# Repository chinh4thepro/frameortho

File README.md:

# frameortho
testing out if a custom keyboard for a framework 13 would work. based off of sweep, slightly modified.

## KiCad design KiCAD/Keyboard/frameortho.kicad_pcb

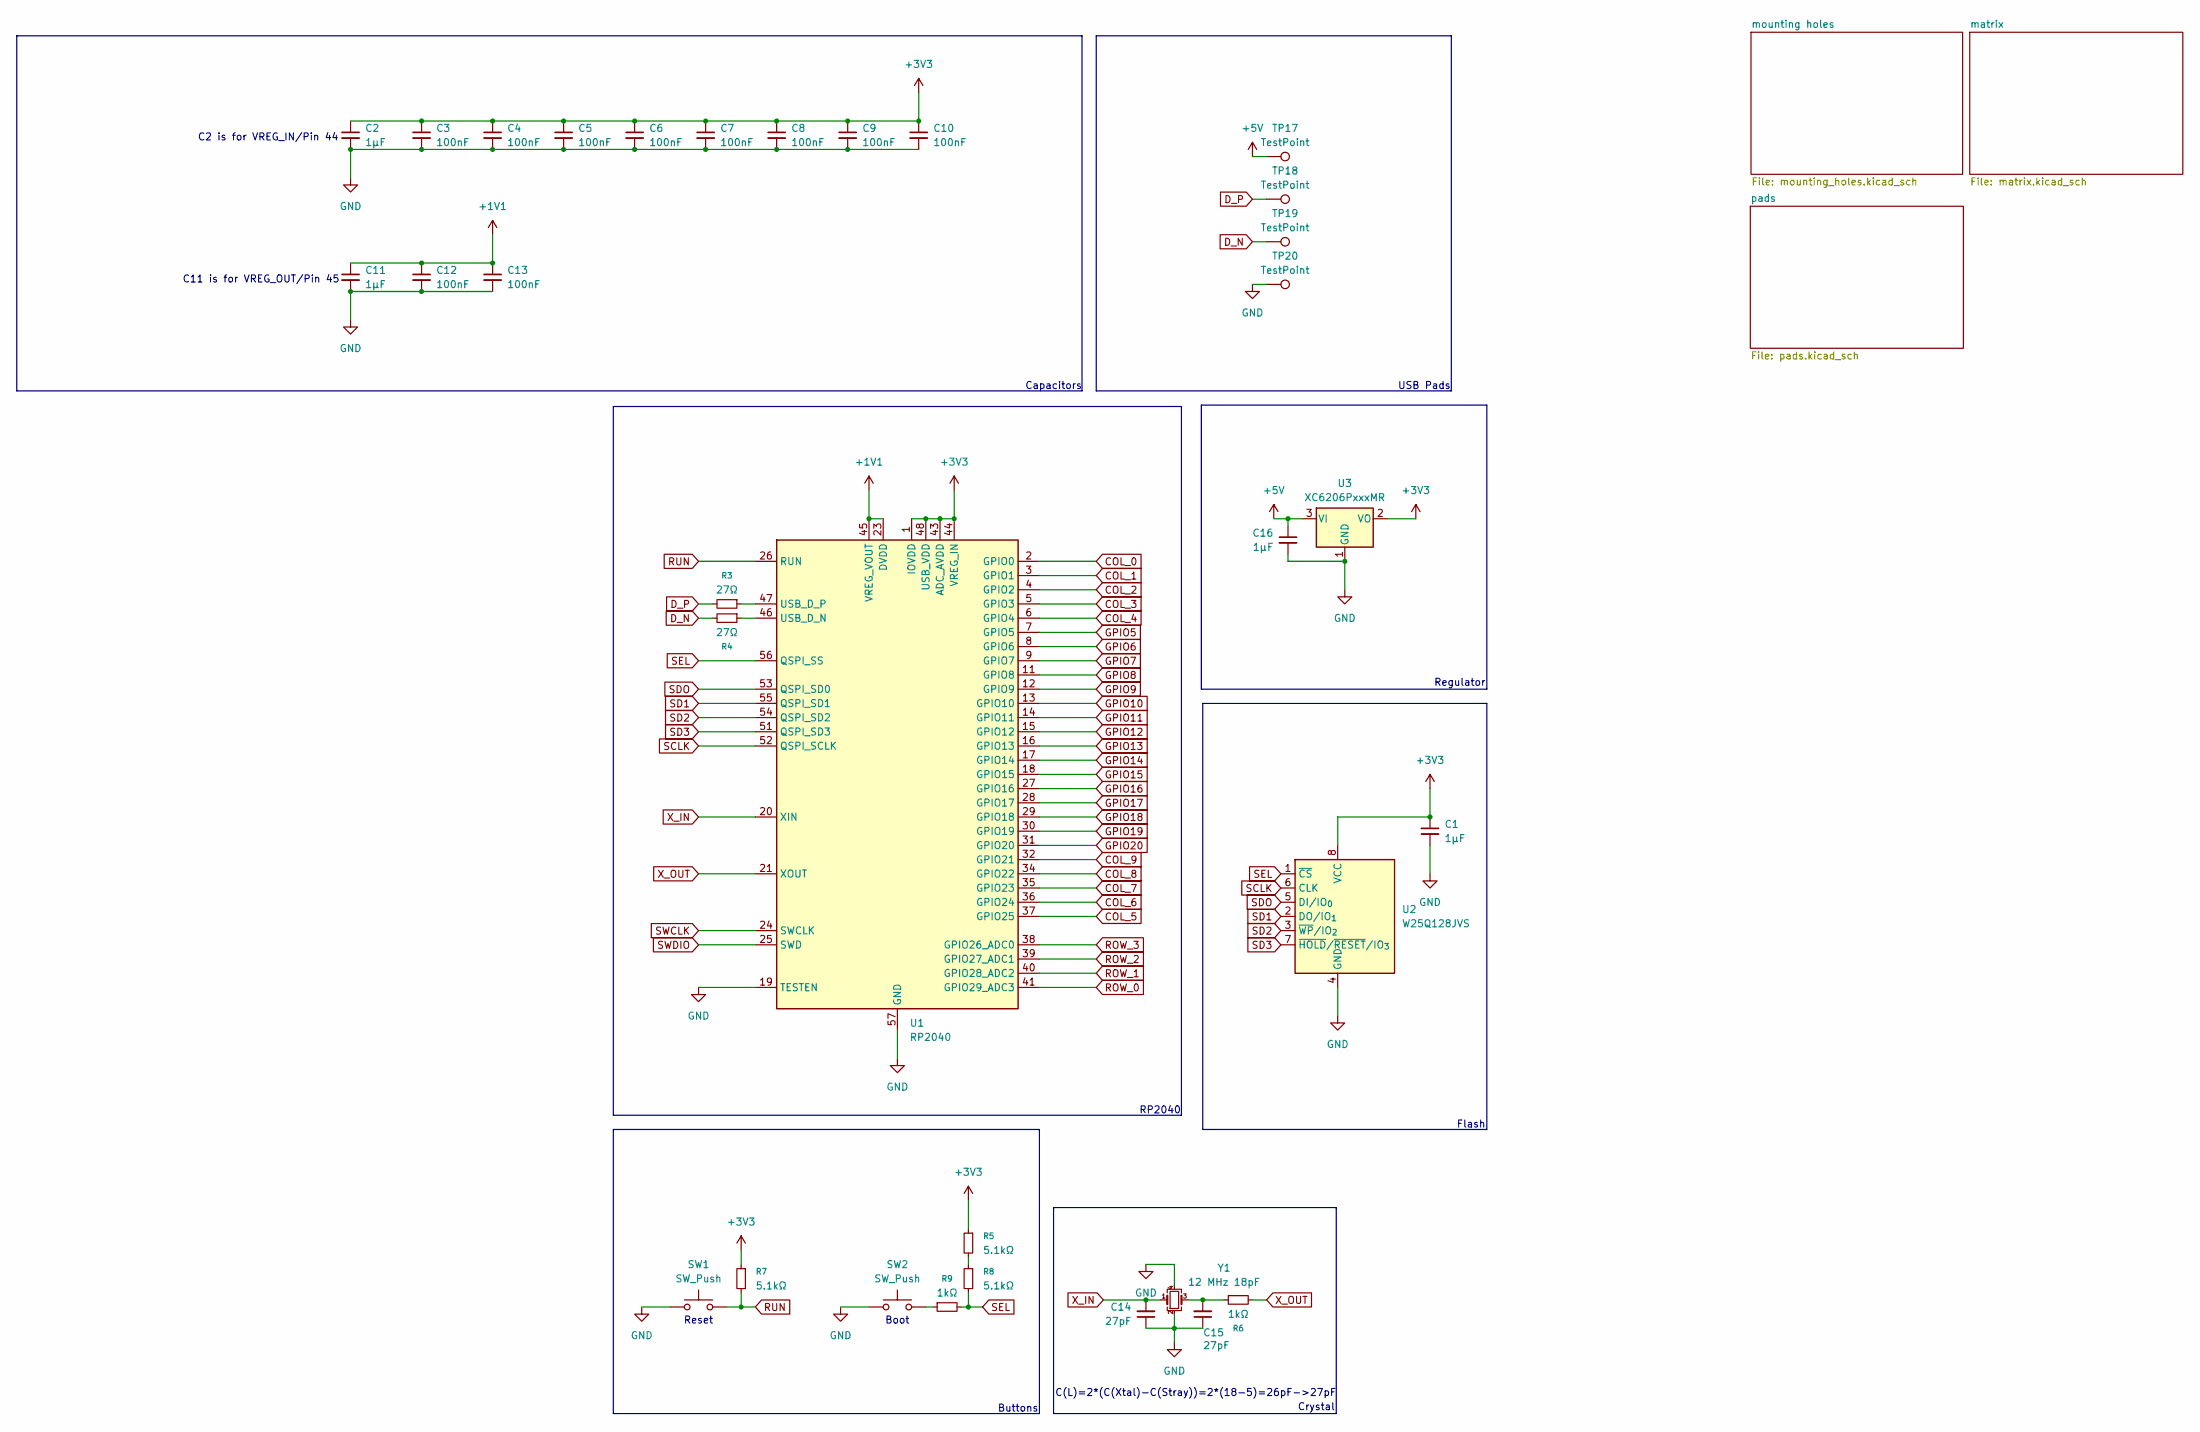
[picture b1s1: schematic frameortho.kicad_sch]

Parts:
C1, C2, C11, C16: 1µF; C_0402_1005Metric
C3, C4, C5, C6, C7, C8, C9, C10, C12, C13: 100nF; C_0402_1005Metric
C14, C15: 27pF; C_0402_1005Metric
R3, R4: 27Ω; R_0402_1005Metric
R5, R7, R8: 5.1kΩ; R_0402_1005Metric
R6, R9: 1kΩ; R_0402_1005Metric
SW1, SW2: SW_Push; Button_TL3342
TP17, TP18, TP19, TP20: TestPoint; TestPoint_Pad_D2.0mm
U1: RP2040; QFN-56-1EP_7x7mm_P0.4mm_EP3.2x3.2mm
U2: W25Q128JVS; SOIC-8_5.3x5.3mm_P1.27mm
U3: XC6206PxxxMR; SOT-23-3
Y1: 12 MHz 18pF; Crystal_SMD_Abracon_ABM3B-4Pin_5.0x3.2mm

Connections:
+1V1: C11.1, C12.1, C13.1, U1.23 (DVDD), U1.45 (VREG_VOUT), U1.50 (DVDD); also elsewhere on the board
+3V3: C1.1, C2.1, C3.1, C4.1, C5.1, C6.1, C7.1, C8.1, C9.1, C10.1, R5.1, R7.1, U1.1 (IOVDD), U1.10 (IOVDD), U1.22 (IOVDD), U1.33 (IOVDD), U1.42 (IOVDD), U1.43 (ADC_AVDD), U1.44 (VREG_IN), U1.48 (USB_VDD), U1.49 (IOVDD), U2.8 (VCC), U3.2 (VO); also elsewhere on the board
+5V: C16.1, TP17.1, U3.3 (VI)
COL_0: U1.2 (GPIO0); also elsewhere on the board
COL_1: U1.3 (GPIO1); also elsewhere on the board
COL_2: U1.4 (GPIO2); also elsewhere on the board
COL_3: U1.5 (GPIO3); also elsewhere on the board
COL_4: U1.6 (GPIO4); also elsewhere on the board
COL_5: U1.37 (GPIO25); also elsewhere on the board
COL_6: U1.36 (GPIO24); also elsewhere on the board
COL_7: U1.35 (GPIO23); also elsewhere on the board
COL_8: U1.34 (GPIO22); also elsewhere on the board
COL_9: U1.32 (GPIO21); also elsewhere on the board
D_N: R4.2, TP19.1
D_P: R3.2, TP18.1
GND: C1.2, C2.2, C3.2, C4.2, C5.2, C6.2, C7.2, C8.2, C9.2, C10.2, C11.2, C12.2, C13.2, C14.1, C15.1, C16.2, SW1.1, SW2.1, TP20.1, U1.19 (TESTEN), U1.57 (GND), U2.4 (GND), U3.1 (GND), Y1.2, Y1.4; also elsewhere on the board
GPIO5: U1.7 (GPIO5); also elsewhere on the board
GPIO6: U1.8 (GPIO6); also elsewhere on the board
GPIO7: U1.9 (GPIO7); also elsewhere on the board
GPIO8: U1.11 (GPIO8); also elsewhere on the board
GPIO9: U1.12 (GPIO9); also elsewhere on the board
GPIO10: U1.13 (GPIO10); also elsewhere on the board
GPIO11: U1.14 (GPIO11); also elsewhere on the board
GPIO12: U1.15 (GPIO12); also elsewhere on the board
GPIO13: U1.16 (GPIO13); also elsewhere on the board
GPIO14: U1.17 (GPIO14); also elsewhere on the board
GPIO15: U1.18 (GPIO15); also elsewhere on the board
GPIO16: U1.27 (GPIO16); also elsewhere on the board
GPIO17: U1.28 (GPIO17); also elsewhere on the board
GPIO18: U1.29 (GPIO18); also elsewhere on the board
GPIO19: U1.30 (GPIO19); also elsewhere on the board
GPIO20: U1.31 (GPIO20); also elsewhere on the board
unnamed: C15.2, R6.1, Y1.3
unnamed: R5.2, R8.1
unnamed: R9.1, SW2.2
unnamed: R4.1, U1.46 (USB_D_N)
unnamed: R3.1, U1.47 (USB_D_P)
ROW_0: U1.41 (GPIO29_ADC3); also elsewhere on the board
ROW_1: U1.40 (GPIO28_ADC2); also elsewhere on the board
ROW_2: U1.39 (GPIO27_ADC1); also elsewhere on the board
ROW_3: U1.38 (GPIO26_ADC0); also elsewhere on the board
RUN: R7.2, SW1.2, U1.26 (RUN)
SCLK: U1.52 (QSPI_SCLK), U2.6 (CLK)
SD1: U1.55 (QSPI_SD1), U2.2 (DO/IO_{1})
SD2: U1.54 (QSPI_SD2), U2.3 (~WP/IO_{2})
SD3: U1.51 (QSPI_SD3), U2.7 (~HOLD/~RESET/IO_{3})
SDO: U1.53 (QSPI_SD0), U2.5 (DI/IO_{0})
SEL: R8.2, R9.2, U1.56 (QSPI_SS), U2.1 (~CS)
SWCLK: U1.24 (SWCLK); also elsewhere on the board
SWDIO: U1.25 (SWD); also elsewhere on the board
X_IN: C14.2, U1.20 (XIN), Y1.1
X_OUT: R6.2, U1.21 (XOUT)

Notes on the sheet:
Reset
C2 is for VREG_IN/Pin 44
USB Pads
Crystal
C11 is for VREG_OUT/Pin 45
Flash
Capacitors
Buttons
Regulator
RP2040
Boot
C(L)=2*(C(Xtal)-C(Stray))=2*(18-5)=26pF->27pF

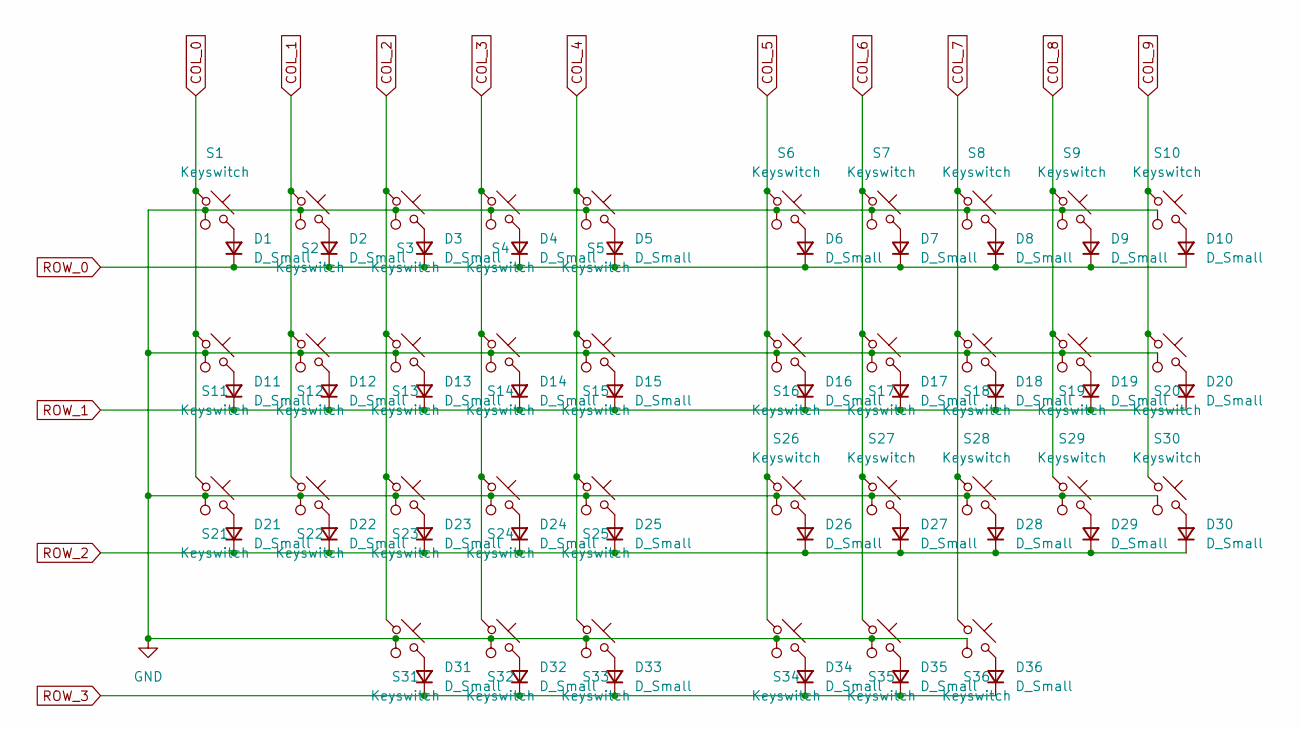
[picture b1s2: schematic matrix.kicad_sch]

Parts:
D1, D2, D3, D4, D5, D6, D7, D8, D9, D10, D11, D12, D13, D14, D15, D16, D17, D18, D19, D20, D21, D22, D23, D24, D25, D26, D27, D28, D29, D30, D31, D32, D33, D34, D35, D36: D_Small; Diode_SOD-123
S1, S2, S3, S4, S5, S6, S7, S8, S9, S10, S11, S12, S13, S14, S15, S16, S17, S18, S19, S20, S21, S22, S23, S24, S25, S26, S27, S28, S29, S30, S31, S32, S33, S34, S35, S36: Keyswitch; CPG1316S01D02_castelated_mikecinq

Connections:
COL_0: S1.1, S11.1, S21.1; also elsewhere on the board
COL_1: S2.1, S12.1, S22.1; also elsewhere on the board
COL_2: S3.1, S13.1, S23.1, S31.1; also elsewhere on the board
COL_3: S4.1, S14.1, S24.1, S32.1; also elsewhere on the board
COL_4: S5.1, S15.1, S25.1, S33.1; also elsewhere on the board
COL_5: S6.1, S16.1, S26.1, S34.1; also elsewhere on the board
COL_6: S7.1, S17.1, S27.1, S35.1; also elsewhere on the board
COL_7: S8.1, S18.1, S28.1, S36.1; also elsewhere on the board
COL_8: S9.1, S19.1, S29.1; also elsewhere on the board
COL_9: S10.1, S20.1, S30.1; also elsewhere on the board
GND: S1.3, S2.3, S3.3, S4.3, S5.3, S6.3, S7.3, S8.3, S9.3, S10.3, S11.3, S12.3, S13.3, S14.3, S15.3, S16.3, S17.3, S18.3, S19.3, S20.3, S21.3, S22.3, S23.3, S24.3, S25.3, S26.3, S27.3, S28.3, S29.3, S30.3, S31.3, S32.3, S33.3, S34.3, S35.3, S36.3; also elsewhere on the board
unnamed: D1.2 (A), S1.2
unnamed: D2.2 (A), S2.2
unnamed: D3.2 (A), S3.2
unnamed: D4.2 (A), S4.2
unnamed: D5.2 (A), S5.2
unnamed: D6.2 (A), S6.2
unnamed: D7.2 (A), S7.2
unnamed: D8.2 (A), S8.2
unnamed: D9.2 (A), S9.2
unnamed: D10.2 (A), S10.2
unnamed: D11.2 (A), S11.2
unnamed: D12.2 (A), S12.2
unnamed: D13.2 (A), S13.2
unnamed: D14.2 (A), S14.2
unnamed: D15.2 (A), S15.2
unnamed: D16.2 (A), S16.2
unnamed: D17.2 (A), S17.2
unnamed: D18.2 (A), S18.2
unnamed: D19.2 (A), S19.2
unnamed: D20.2 (A), S20.2
unnamed: D21.2 (A), S21.2
unnamed: D22.2 (A), S22.2
unnamed: D23.2 (A), S23.2
unnamed: D24.2 (A), S24.2
unnamed: D25.2 (A), S25.2
unnamed: D26.2 (A), S26.2
unnamed: D27.2 (A), S27.2
unnamed: D28.2 (A), S28.2
unnamed: D29.2 (A), S29.2
unnamed: D30.2 (A), S30.2
unnamed: D31.2 (A), S31.2
unnamed: D32.2 (A), S32.2
unnamed: D33.2 (A), S33.2
unnamed: D34.2 (A), S34.2
unnamed: D35.2 (A), S35.2
unnamed: D36.2 (A), S36.2
ROW_0: D1.1 (K), D2.1 (K), D3.1 (K), D4.1 (K), D5.1 (K), D6.1 (K), D7.1 (K), D8.1 (K), D9.1 (K), D10.1 (K); also elsewhere on the board
ROW_1: D11.1 (K), D12.1 (K), D13.1 (K), D14.1 (K), D15.1 (K), D16.1 (K), D17.1 (K), D18.1 (K), D19.1 (K), D20.1 (K); also elsewhere on the board
ROW_2: D21.1 (K), D22.1 (K), D23.1 (K), D24.1 (K), D25.1 (K), D26.1 (K), D27.1 (K), D28.1 (K), D29.1 (K), D30.1 (K); also elsewhere on the board
ROW_3: D31.1 (K), D32.1 (K), D33.1 (K), D34.1 (K), D35.1 (K), D36.1 (K); also elsewhere on the board

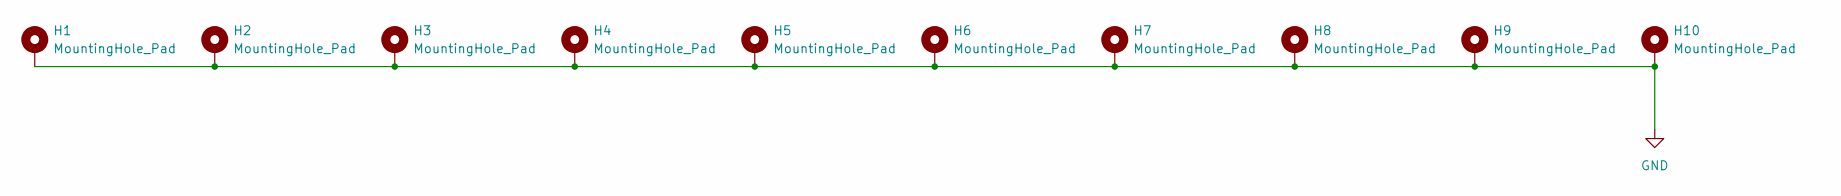
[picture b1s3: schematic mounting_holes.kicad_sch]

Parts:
H1, H2, H3, H4, H5, H6, H7, H8, H9, H10: MountingHole_Pad; MountingHole_2.2mm_M2_DIN965_Pad_TopBottom

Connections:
GND: H1.1, H2.1, H3.1, H4.1, H5.1, H6.1, H7.1, H8.1, H9.1, H10.1; also elsewhere on the board

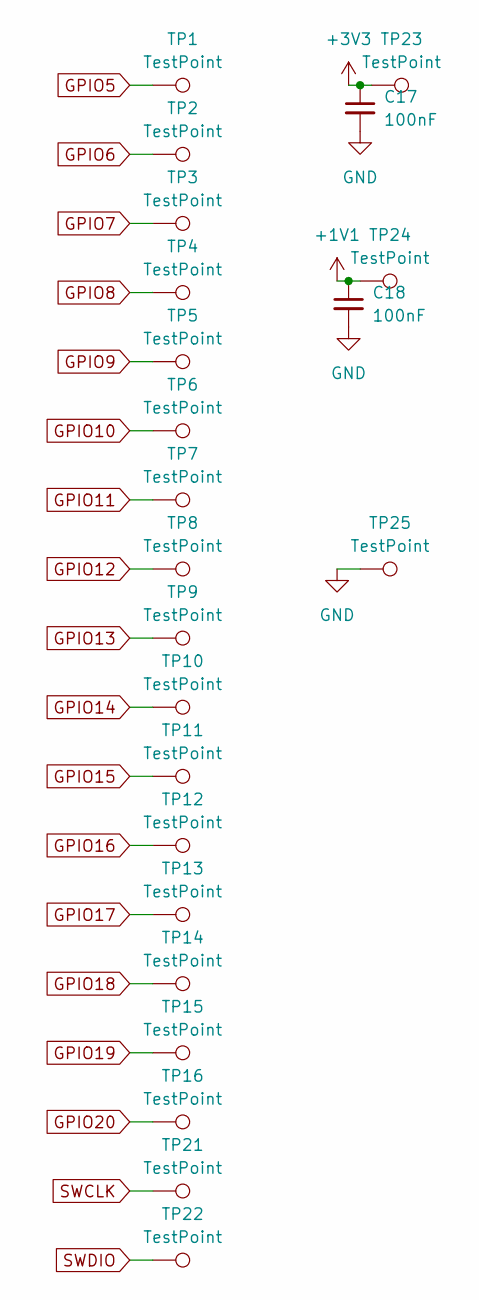
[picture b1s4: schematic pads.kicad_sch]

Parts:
C17, C18: 100nF; C_0402_1005Metric
TP1, TP2, TP3, TP4, TP5, TP6, TP7, TP8, TP9, TP10, TP11, TP12, TP13, TP14, TP15, TP16, TP21, TP22, TP23, TP24, TP25: TestPoint; TestPoint_Pad_D2.0mm

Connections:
+1V1: C18.1, TP24.1; also elsewhere on the board
+3V3: C17.1, TP23.1; also elsewhere on the board
GND: C17.2, C18.2, TP25.1; also elsewhere on the board
GPIO5: TP1.1; also elsewhere on the board
GPIO6: TP2.1; also elsewhere on the board
GPIO7: TP3.1; also elsewhere on the board
GPIO8: TP4.1; also elsewhere on the board
GPIO9: TP5.1; also elsewhere on the board
GPIO10: TP6.1; also elsewhere on the board
GPIO11: TP7.1; also elsewhere on the board
GPIO12: TP8.1; also elsewhere on the board
GPIO13: TP9.1; also elsewhere on the board
GPIO14: TP10.1; also elsewhere on the board
GPIO15: TP11.1; also elsewhere on the board
GPIO16: TP12.1; also elsewhere on the board
GPIO17: TP13.1; also elsewhere on the board
GPIO18: TP14.1; also elsewhere on the board
GPIO19: TP15.1; also elsewhere on the board
GPIO20: TP16.1; also elsewhere on the board
SWCLK: TP21.1; also elsewhere on the board
SWDIO: TP22.1; also elsewhere on the board

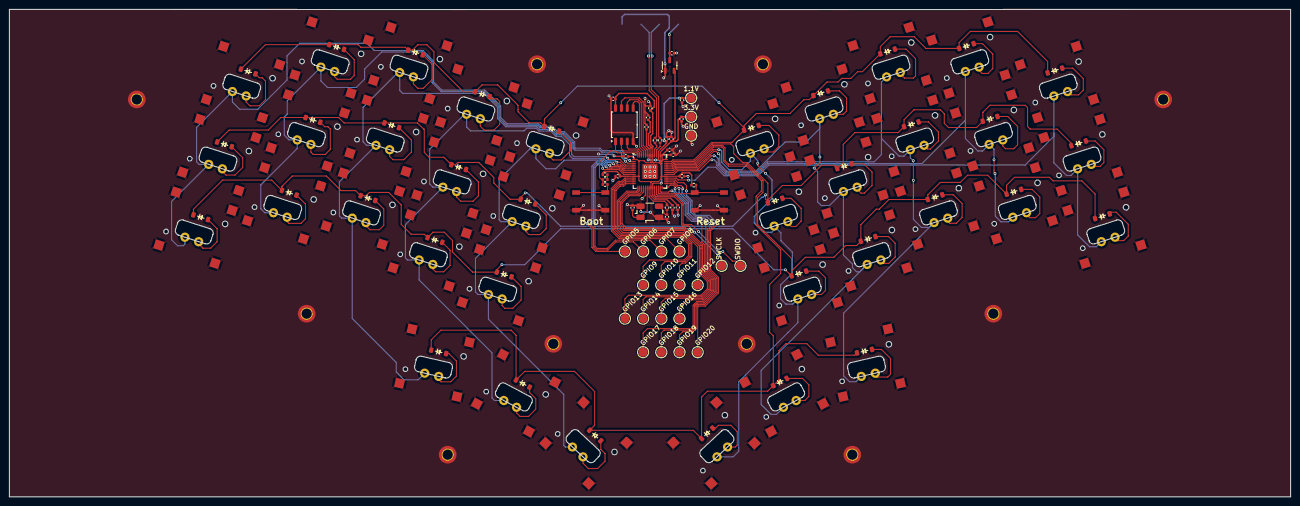
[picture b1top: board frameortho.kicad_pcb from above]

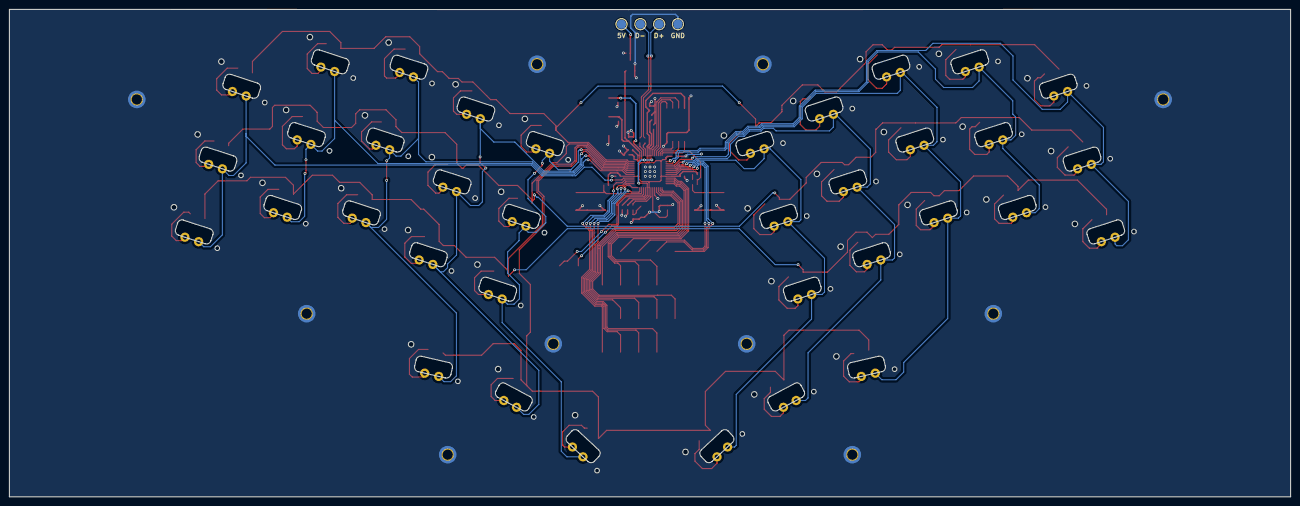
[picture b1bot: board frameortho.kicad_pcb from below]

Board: 2 copper layers, 275.9 x 105.0 mm, 138 parts (4 on the bottom side), 88 nets.

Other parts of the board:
1.1V, 3.3V: TestPoint; TestPoint_Pad_D2.0mm
GND: TestPoint; TestPoint_Pad_D2.0mm

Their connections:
+1V1: 1.1V.1; also elsewhere on the board
+3V3: 3.3V.1; also elsewhere on the board
GND: GND.1; also elsewhere on the board

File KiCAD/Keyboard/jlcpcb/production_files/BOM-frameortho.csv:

Comment,Designator,Footprint,LCSC,Quantity
XC6206PxxxMR,U3,SOT-23-3,,1
W25Q128JVS,U2,SOIC-8_5.3x5.3mm_P1.27mm,,1
RP2040,U1,QFN-56-1EP_7x7mm_P0.4mm_EP3.2x3.2mm,,1
Keyswitch,S36,CPG1316S01D02_castelated_mikecinq,,1
Keyswitch,S35,CPG1316S01D02_castelated_mikecinq,,1
Keyswitch,S34,CPG1316S01D02_castelated_mikecinq,,1
Keyswitch,S33,CPG1316S01D02_castelated_mikecinq,,1
Keyswitch,S32,CPG1316S01D02_castelated_mikecinq,,1
Keyswitch,S31,CPG1316S01D02_castelated_mikecinq,,1
Keyswitch,S30,CPG1316S01D02_castelated_mikecinq,,1
Keyswitch,S29,CPG1316S01D02_castelated_mikecinq,,1
Keyswitch,S28,CPG1316S01D02_castelated_mikecinq,,1
Keyswitch,S27,CPG1316S01D02_castelated_mikecinq,,1
Keyswitch,S26,CPG1316S01D02_castelated_mikecinq,,1
Keyswitch,S25,CPG1316S01D02_castelated_mikecinq,,1
Keyswitch,S24,CPG1316S01D02_castelated_mikecinq,,1
Keyswitch,S23,CPG1316S01D02_castelated_mikecinq,,1
Keyswitch,S22,CPG1316S01D02_castelated_mikecinq,,1
Keyswitch,S21,CPG1316S01D02_castelated_mikecinq,,1
Keyswitch,S20,CPG1316S01D02_castelated_mikecinq,,1
Keyswitch,S19,CPG1316S01D02_castelated_mikecinq,,1
Keyswitch,S18,CPG1316S01D02_castelated_mikecinq,,1
Keyswitch,S17,CPG1316S01D02_castelated_mikecinq,,1
Keyswitch,S16,CPG1316S01D02_castelated_mikecinq,,1
Keyswitch,S15,CPG1316S01D02_castelated_mikecinq,,1
Keyswitch,S14,CPG1316S01D02_castelated_mikecinq,,1
Keyswitch,S13,CPG1316S01D02_castelated_mikecinq,,1
Keyswitch,S12,CPG1316S01D02_castelated_mikecinq,,1
Keyswitch,S11,CPG1316S01D02_castelated_mikecinq,,1
Keyswitch,S10,CPG1316S01D02_castelated_mikecinq,,1
Keyswitch,S9,CPG1316S01D02_castelated_mikecinq,,1
Keyswitch,S8,CPG1316S01D02_castelated_mikecinq,,1
Keyswitch,S7,CPG1316S01D02_castelated_mikecinq,,1
Keyswitch,S6,CPG1316S01D02_castelated_mikecinq,,1
Keyswitch,S5,CPG1316S01D02_castelated_mikecinq,,1
Keyswitch,S4,CPG1316S01D02_castelated_mikecinq,,1
Keyswitch,S3,CPG1316S01D02_castelated_mikecinq,,1
Keyswitch,S2,CPG1316S01D02_castelated_mikecinq,,1
Keyswitch,S1,CPG1316S01D02_castelated_mikecinq,,1
1µF,C1,C_0402_1005Metric,,1
D_Small,D36,Diode_SOD-123,,1
D_Small,D2,Diode_SOD-123,,1
D_Small,D28,Diode_SOD-123,,1
D_Small,D9,Diode_SOD-123,,1
TestPoint,TP6,TestPoint_Pad_D2.0mm,,1
D_Small,D24,Diode_SOD-123,,1
5.1kΩ,R5,R_0402_1005Metric,,1
TestPoint,TP11,TestPoint_Pad_D2.0mm,,1
D_Small,D22,Diode_SOD-123,,1
TestPoint,TP14,TestPoint_Pad_D2.0mm,,1
D_Small,D14,Diode_SOD-123,,1
12 MHz 20pF,Y1,Crystal_SMD_Abracon_ABM3B-4Pin_5.0x3.2mm,,1
TestPoint,TP10,TestPoint_Pad_D2.0mm,,1
TestPoint,TP1,TestPoint_Pad_D2.0mm,,1
TestPoint,TP9,TestPoint_Pad_D2.0mm,,1
D_Small,D25,Diode_SOD-123,,1
TestPoint,TP7,TestPoint_Pad_D2.0mm,,1
100nF,C9,C_0402_1005Metric,,1
27Ω,R3,R_0402_1005Metric,,1
TestPoint,TP22,TestPoint_Pad_D2.0mm,,1
D_Small,D4,Diode_SOD-123,,1
D_Small,D33,Diode_SOD-123,,1
D_Small,D18,Diode_SOD-123,,1
D_Small,D35,Diode_SOD-123,,1
TestPoint,TP4,TestPoint_Pad_D2.0mm,,1
D_Small,D8,Diode_SOD-123,,1
SW_Push,SW1,Button_TL3342,,1
TestPoint,TP16,TestPoint_Pad_D2.0mm,,1
D_Small,D11,Diode_SOD-123,,1
D_Small,D16,Diode_SOD-123,,1
1kΩ,R9,R_0402_1005Metric,,1
D_Small,D15,Diode_SOD-123,,1
D_Small,D31,Diode_SOD-123,,1
D_Small,D32,Diode_SOD-123,,1
1kΩ,R6,R_0402_1005Metric,,1
100nF,C5,C_0402_1005Metric,,1
TestPoint,TP15,TestPoint_Pad_D2.0mm,,1
TestPoint,TP12,TestPoint_Pad_D2.0mm,,1
D_Small,D20,Diode_SOD-123,,1
D_Small,D17,Diode_SOD-123,,1
100nF,C7,C_0402_1005Metric,,1
TestPoint,TP5,TestPoint_Pad_D2.0mm,,1
100nF,C12,C_0402_1005Metric,,1
D_Small,D34,Diode_SOD-123,,1
100nF,C10,C_0402_1005Metric,,1
100nF,C3,C_0402_1005Metric,,1
D_Small,D21,Diode_SOD-123,,1
D_Small,D13,Diode_SOD-123,,1
TestPoint,TP2,TestPoint_Pad_D2.0mm,,1
33pF,C14,C_0402_1005Metric,,1
5.1kΩ,R7,R_0402_1005Metric,,1
100nF,C4,C_0402_1005Metric,,1
D_Small,D23,Diode_SOD-123,,1
TestPoint,TP21,TestPoint_Pad_D2.0mm,,1
27Ω,R4,R_0402_1005Metric,,1
D_Small,D3,Diode_SOD-123,,1
TestPoint,TP8,TestPoint_Pad_D2.0mm,,1
D_Small,D26,Diode_SOD-123,,1
SW_Push,SW2,Button_TL3342,,1
1µF,C11,C_0402_1005Metric,,1
D_Small,D10,Diode_SOD-123,,1
TestPoint,TP13,TestPoint_Pad_D2.0mm,,1
1µF,C2,C_0402_1005Metric,,1
33pF,C15,C_0402_1005Metric,,1
TestPoint,TP3,TestPoint_Pad_D2.0mm,,1
100nF,C6,C_0402_1005Metric,,1
5.1kΩ,R8,R_0402_1005Metric,,1
D_Small,D7,Diode_SOD-123,,1
D_Small,D27,Diode_SOD-123,,1
D_Small,D30,Diode_SOD-123,,1
D_Small,D5,Diode_SOD-123,,1
100nF,C13,C_0402_1005Metric,,1
D_Small,D19,Diode_SOD-123,,1
100nF,C8,C_0402_1005Metric,,1
D_Small,D1,Diode_SOD-123,,1
D_Small,D6,Diode_SOD-123,,1
D_Small,D29,Diode_SOD-123,,1
D_Small,D12,Diode_SOD-123,,1
TestPoint,TP20,TestPoint_Pad_D2.0mm,,1
TestPoint,TP18,TestPoint_Pad_D2.0mm,,1
TestPoint,TP17,TestPoint_Pad_D2.0mm,,1
TestPoint,TP19,TestPoint_Pad_D2.0mm,,1

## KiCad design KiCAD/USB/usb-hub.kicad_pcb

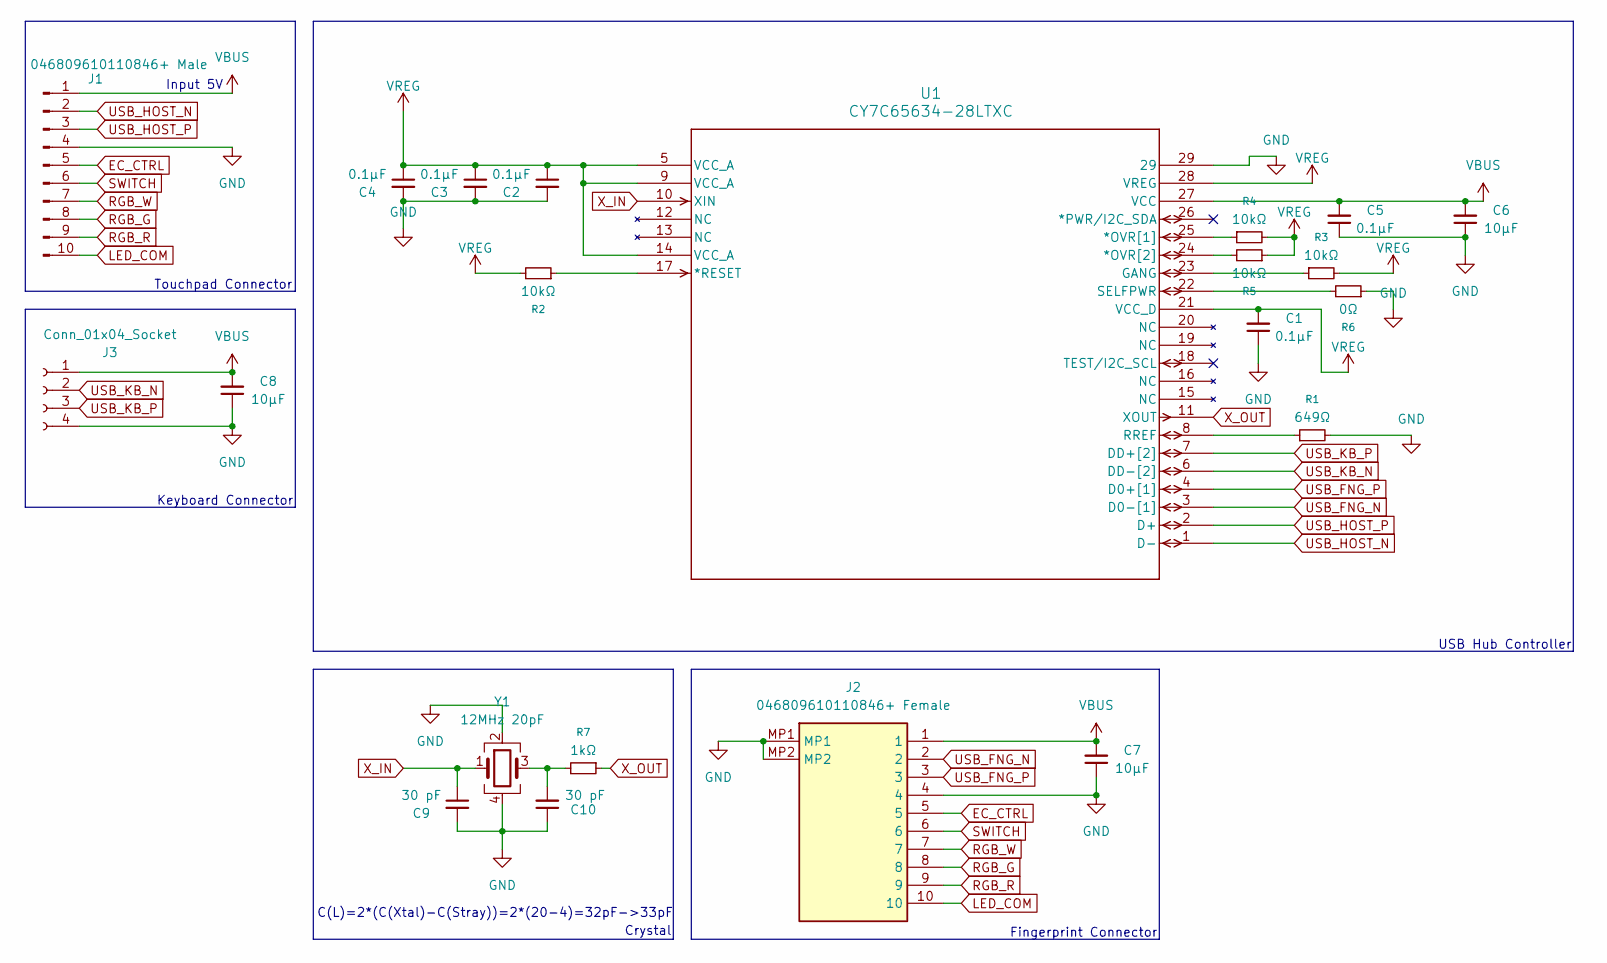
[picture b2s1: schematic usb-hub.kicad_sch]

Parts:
C1, C2, C3, C4, C5: 0.1μF; C_0402_1005Metric
C6, C7, C8: 10μF; C_0402_1005Metric
C9, C10: 30 pF; C_0402_1005Metric
J1: 046809610110846+ Male; Kyocera_046809610110846+_PCB_Edge
J2: 046809610110846+ Female; 046809610110846; Manufacturer_Part_Number 046809610110846+; Mouser Part Number 346-046809610110846+
J3: Conn_01x04_Socket; 4 pad
R1: 649Ω; R_0402_1005Metric
R2, R3, R4, R5: 10kΩ; R_0402_1005Metric
R6: 0Ω; R_0402_1005Metric
R7: 1kΩ; R_0402_1005Metric
U1: CY7C65634-28LTXC; QFN-28
Y1: 12MHz 20pF; Crystal_SMD_Abracon_ABM3B-4Pin_5.0x3.2mm

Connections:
EC_CTRL: J1.5, J2.5
GND: C1.1, C2.2, C3.2, C4.2, C5.1, C6.1, C7.1, C8.1, C9.2, C10.1, J1.4, J2.4, J2.MP1, J2.MP2, J3.4, R1.2, R6.1, U1.29, Y1.2, Y1.4
LED_COM: J1.10, J2.10
unnamed: C10.2, R7.2, Y1.3
unnamed: R4.1, U1.25 (*OVR[1])
unnamed: R5.2, U1.24 (*OVR[2])
unnamed: R2.1, U1.17 (*RESET)
unnamed: R3.1, U1.23 (GANG)
unnamed: R1.1, U1.8 (RREF)
unnamed: R6.2, U1.22 (SELFPWR)
RGB_G: J1.8, J2.8
RGB_R: J1.9, J2.9
RGB_W: J1.7, J2.7
SWITCH: J1.6, J2.6
USB_FNG_N: J2.2, U1.3 (D0-[1])
USB_FNG_P: J2.3, U1.4 (D0+[1])
USB_HOST_N: J1.2, U1.1 (D-)
USB_HOST_P: J1.3, U1.2 (D+)
USB_KB_N: J3.2, U1.6 (DD-[2])
USB_KB_P: J3.3, U1.7 (DD+[2])
VBUS: C5.2, C6.2, C7.2, C8.2, J1.1, J2.1, J3.1, U1.27 (VCC)
VREG: C1.2, C2.1, C3.1, C4.1, R2.2, R3.2, R4.2, R5.1, U1.5 (VCC_A), U1.9 (VCC_A), U1.14 (VCC_A), U1.21 (VCC_D), U1.28 (VREG)
X_IN: C9.1, U1.10 (XIN), Y1.1
X_OUT: R7.1, U1.11 (XOUT)

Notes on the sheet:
USB Hub Controller
Keyboard Connector
Crystal
Touchpad Connector
Fingerprint Connector
C(L)=2*(C(Xtal)-C(Stray))=2*(20-4)=32pF->33pF
Input 5V

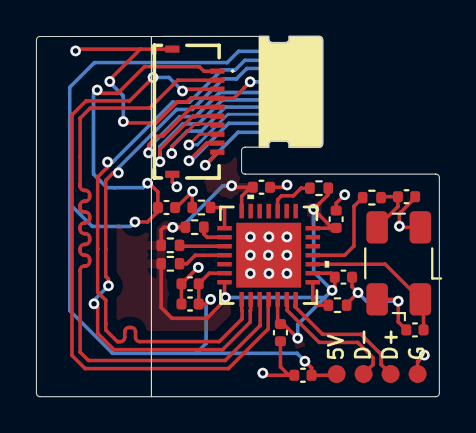
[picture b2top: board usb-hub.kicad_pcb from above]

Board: 2 copper layers, 22.4 x 20.0 mm, 22 parts (0 on the bottom side), 24 nets.

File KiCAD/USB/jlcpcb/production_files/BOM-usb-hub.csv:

Comment,Designator,Footprint,LCSC,Quantity
30 pF,"C10,C9",C_0402_1005Metric,C107004,2
0.1μF,"C1,C2,C3,C4,C5",C_0402_1005Metric,C133086,5
CY7C65634-28LTXC,U1,QFN-28,C2951393,1
10μF,"C6,C7,C8",C_0402_1005Metric,C315248,3
046809610110846+ Male,J1,Kyocera_046809610110846+_PCB_Edge,C5464531,1
12MHz 20pF,Y1,Crystal_SMD_Abracon_ABM3B-4Pin_5.0x3.2mm,C596868,1
10kΩ,"R2,R3,R4,R5",R_0402_1005Metric,C71617,4
1kΩ,R7,R_0402_1005Metric,C71623,1
649Ω,R1,R_0402_1005Metric,C881120,1
0Ω,R6,R_0402_1005Metric,C881153,1

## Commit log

2025-09-10 i need sleep
2025-09-11 set up connectors
2025-09-12 mmmm... usb hub controller...
2025-09-12 submodule
2025-09-12 gitty ignore
2025-09-12 clean up schematic, add clock
2025-09-13 change symbol
2025-09-13 oh the license doesn't allow this...
2025-09-13 fix captialization
2025-09-13 male kyocera connector
2025-09-13 stuff
2025-09-14 stuffs
2025-09-14 Finish USB hub pcb
2025-09-14 why wasn't this staged
2025-09-14 start work on keyboard
2025-09-14 gitty submodules
2025-09-14 move stuff and fix constraints
2025-09-14 production files + goldfinger
2025-09-15 ofc i had to be using the wrong footprint
2025-09-15 forgor to tune differential pair traces
2025-09-15 move vbus capacitor
2025-09-15 idk if submodules worked
2025-09-16 stiffener
2025-09-16 what
2025-09-16 add submodule
2025-09-16 ergogen/layout
2025-09-17 start keyboard pcb
2025-09-18 mostly finished pcb
2025-09-18 changes ig
2025-09-18 update some stuff
2025-09-19 idk what i did tbh
2025-09-21 why no commit
2025-09-21 whatever
2025-10-23 mounting holes
2025-11-11 this aint supposed to be here
2025-11-12 why is ts still here
2025-11-21 i dont care anymore
2025-11-22 most of the edp to dp
